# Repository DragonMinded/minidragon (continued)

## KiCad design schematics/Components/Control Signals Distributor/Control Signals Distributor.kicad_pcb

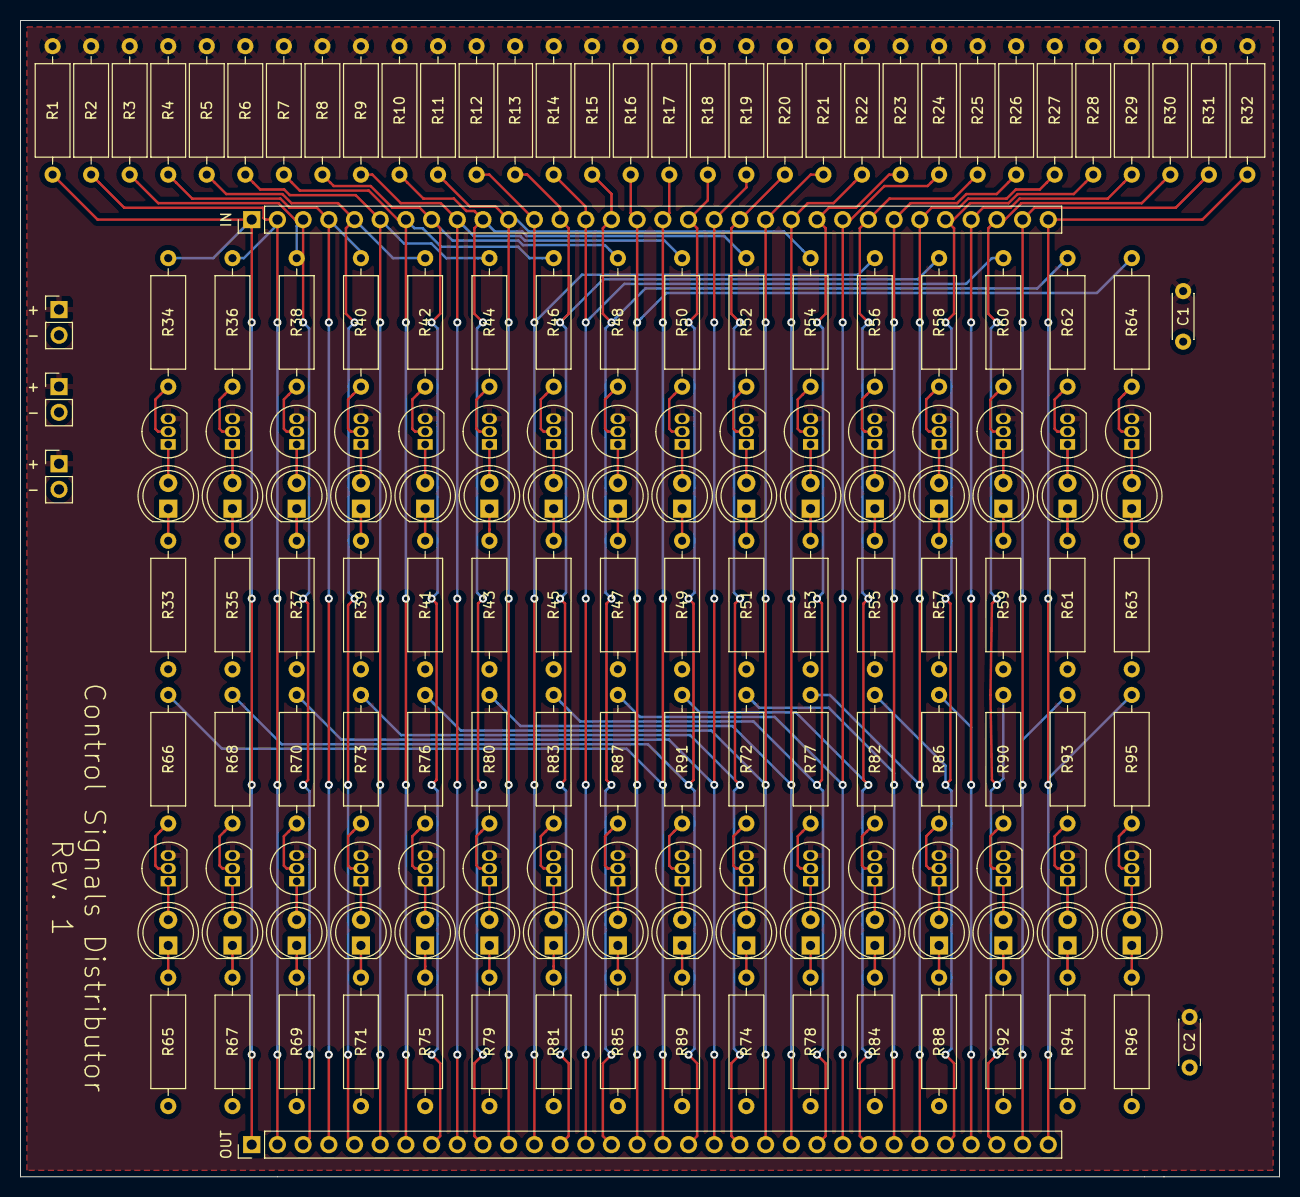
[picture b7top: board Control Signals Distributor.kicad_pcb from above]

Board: 2 copper layers, 124.5 x 114.3 mm, 167 parts (0 on the bottom side), 130 nets.

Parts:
C1, C2: 0.1uF; C_Disc_D4.3mm_W1.9mm_P5.00mm
D1, D2, D3, D4, D5, D6, D7, D8, D9, D10, D11, D12, D13, D14, D15, D16, D17, D18, D19, D20, D21, D22, D23, D24, D25, D26, D27, D28, D29, D30, D31, D32: LED; LED_D5.0mm
J1, J3, J4: POWER; PinHeader_1x02_P2.54mm_Vertical
J2: IN; PinHeader_1x32_P2.54mm_Vertical
J5: OUT; PinHeader_1x32_P2.54mm_Vertical
Q1, Q2, Q3, Q4, Q5, Q6, Q7, Q8, Q9, Q10, Q11, Q12, Q13, Q14, Q15, Q16, Q17, Q18, Q19, Q20, Q21, Q22, Q23, Q24, Q25, Q26, Q27, Q28, Q29, Q30, Q31, Q32: 2N2222; TO-92_Inline
R1, R2, R3, R4, R5, R6, R7, R8, R9, R10, R11, R12, R13, R14, R15, R16, R17, R18, R19, R20, R21, R22, R23, R24, R25, R26, R27, R28, R29, R30, R31, R32, R33, R35, R37, R39, R41, R43, R45, R47, R49, R51, R53, R55, R57, R59, R61, R63, R65, R67, R69, R71, R74, R75, R78, R79, R81, R84, R85, R88, R89, R92, R94, R96: 1K; R_Axial_DIN0309_L9.0mm_D3.2mm_P12.70mm_Horizontal
R34, R36, R38, R40, R42, R44, R46, R48, R50, R52, R54, R56, R58, R60, R62, R64, R66, R68, R70, R72, R73, R76, R77, R80, R82, R83, R86, R87, R90, R91, R93, R95: 10K; R_Axial_DIN0309_L9.0mm_D3.2mm_P12.70mm_Horizontal

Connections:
GND: C1.2, C2.2, J1.2, J3.2, J4.2, R33.2, R35.2, R37.2, R39.2, R41.2, R43.2, R45.2, R47.2, R49.2, R51.2, R53.2, R55.2, R57.2, R59.2, R61.2, R63.2, R65.2, R67.2, R69.2, R71.2, R74.2, R75.2, R78.2, R79.2, R81.2, R84.2, R85.2, R88.2, R89.2, R92.2, R94.2, R96.2
unnamed: D1.2 (A), Q1.1 (E)
unnamed: D1.1 (K), R33.1
unnamed: D2.2 (A), Q2.1 (E)
unnamed: D2.1 (K), R35.1
unnamed: D3.2 (A), Q3.1 (E)
unnamed: D3.1 (K), R37.1
unnamed: D4.2 (A), Q4.1 (E)
unnamed: D4.1 (K), R39.1
unnamed: D5.2 (A), Q5.1 (E)
unnamed: D5.1 (K), R41.1
unnamed: D6.2 (A), Q6.1 (E)
unnamed: D6.1 (K), R43.1
unnamed: D7.2 (A), Q7.1 (E)
unnamed: D7.1 (K), R45.1
unnamed: D8.2 (A), Q8.1 (E)
unnamed: D8.1 (K), R47.1
unnamed: D9.2 (A), Q9.1 (E)
unnamed: D9.1 (K), R49.1
unnamed: D10.2 (A), Q10.1 (E)
unnamed: D10.1 (K), R51.1
unnamed: D11.2 (A), Q11.1 (E)
unnamed: D11.1 (K), R53.1
unnamed: D12.2 (A), Q12.1 (E)
unnamed: D12.1 (K), R55.1
unnamed: D13.2 (A), Q13.1 (E)
unnamed: D13.1 (K), R57.1
unnamed: D14.2 (A), Q14.1 (E)
unnamed: D14.1 (K), R59.1
unnamed: D15.2 (A), Q15.1 (E)
unnamed: D15.1 (K), R61.1
unnamed: D16.2 (A), Q16.1 (E)
unnamed: D16.1 (K), R63.1
unnamed: D17.2 (A), Q17.1 (E)
unnamed: D17.1 (K), R65.1
unnamed: D18.2 (A), Q18.1 (E)
unnamed: D18.1 (K), R67.1
unnamed: D19.2 (A), Q19.1 (E)
unnamed: D19.1 (K), R69.1
unnamed: D20.2 (A), Q21.1 (E)
unnamed: D20.1 (K), R71.1
unnamed: D21.2 (A), Q20.1 (E)
unnamed: D21.1 (K), R74.1
unnamed: D22.2 (A), Q22.1 (E)
unnamed: D22.1 (K), R75.1
unnamed: D23.2 (A), Q23.1 (E)
unnamed: D23.1 (K), R78.1
unnamed: D24.2 (A), Q24.1 (E)
unnamed: D24.1 (K), R79.1
unnamed: D25.2 (A), Q26.1 (E)
unnamed: D25.1 (K), R81.1
unnamed: D26.2 (A), Q25.1 (E)
unnamed: D26.1 (K), R84.1
unnamed: D27.2 (A), Q28.1 (E)
unnamed: D27.1 (K), R85.1
unnamed: D28.2 (A), Q27.1 (E)
unnamed: D28.1 (K), R88.1
unnamed: D29.2 (A), Q30.1 (E)
unnamed: D29.1 (K), R89.1
unnamed: D30.2 (A), Q29.1 (E)
unnamed: D30.1 (K), R92.1
unnamed: D31.2 (A), Q31.1 (E)
unnamed: D31.1 (K), R94.1
unnamed: D32.2 (A), Q32.1 (E)
unnamed: D32.1 (K), R96.1
unnamed: J2.1, J5.1, R1.2, R34.1
unnamed: J2.2, J5.2, R2.2, R36.1
unnamed: J2.3, J5.3, R3.2, R38.1
unnamed: J2.4, J5.4, R4.2, R40.1
unnamed: J2.5, J5.5, R5.2, R42.1
unnamed: J2.6, J5.6, R6.2, R44.1
unnamed: J2.7, J5.7, R7.2, R46.1
unnamed: J2.8, J5.8, R8.2, R48.1
unnamed: J2.9, J5.9, R9.2, R50.1
unnamed: J2.10, J5.10, R10.2, R52.1
unnamed: J2.11, J5.11, R11.2, R54.1
unnamed: J2.12, J5.12, R12.2, R56.1
unnamed: J2.13, J5.13, R13.2, R58.1
unnamed: J2.14, J5.14, R14.2, R60.1
unnamed: J2.15, J5.15, R15.2, R62.1
unnamed: J2.16, J5.16, R16.2, R64.1
unnamed: J2.17, J5.17, R17.2, R66.1
unnamed: J2.18, J5.18, R18.2, R68.1
unnamed: J2.19, J5.19, R19.2, R70.1
unnamed: J2.20, J5.20, R20.2, R73.1
unnamed: J2.21, J5.21, R21.2, R76.1
unnamed: J2.22, J5.22, R22.2, R80.1
unnamed: J2.23, J5.23, R23.2, R83.1
unnamed: J2.24, J5.24, R24.2, R87.1
unnamed: J2.25, J5.25, R25.2, R91.1
unnamed: J2.26, J5.26, R26.2, R72.1
unnamed: J2.27, J5.27, R27.2, R77.1
unnamed: J2.28, J5.28, R28.2, R82.1
unnamed: J2.29, J5.29, R29.2, R86.1
unnamed: J2.30, J5.30, R30.2, R90.1
unnamed: J2.31, J5.31, R31.2, R93.1
unnamed: J2.32, J5.32, R32.2, R95.1
unnamed: Q1.2 (B), R34.2
unnamed: Q2.2 (B), R36.2
unnamed: Q3.2 (B), R38.2
unnamed: Q4.2 (B), R40.2
unnamed: Q5.2 (B), R42.2
unnamed: Q6.2 (B), R44.2
unnamed: Q7.2 (B), R46.2
unnamed: Q8.2 (B), R48.2
unnamed: Q9.2 (B), R50.2
unnamed: Q10.2 (B), R52.2
unnamed: Q11.2 (B), R54.2
unnamed: Q12.2 (B), R56.2
unnamed: Q13.2 (B), R58.2
unnamed: Q14.2 (B), R60.2
unnamed: Q15.2 (B), R62.2
unnamed: Q16.2 (B), R64.2
unnamed: Q17.2 (B), R66.2
unnamed: Q18.2 (B), R68.2
unnamed: Q19.2 (B), R70.2
unnamed: Q20.2 (B), R72.2
unnamed: Q21.2 (B), R73.2
unnamed: Q22.2 (B), R76.2
unnamed: Q23.2 (B), R77.2
unnamed: Q24.2 (B), R80.2
unnamed: Q25.2 (B), R82.2
unnamed: Q26.2 (B), R83.2
unnamed: Q27.2 (B), R86.2
unnamed: Q28.2 (B), R87.2
unnamed: Q29.2 (B), R90.2
unnamed: Q30.2 (B), R91.2
unnamed: Q31.2 (B), R93.2
unnamed: Q32.2 (B), R95.2
VCC: C1.1, C2.1, J1.1, J3.1, J4.1, Q1.3 (C), Q2.3 (C), Q3.3 (C), Q4.3 (C), Q5.3 (C), Q6.3 (C), Q7.3 (C), Q8.3 (C), Q9.3 (C), Q10.3 (C), Q11.3 (C), Q12.3 (C), Q13.3 (C), Q14.3 (C), Q15.3 (C), Q16.3 (C), Q17.3 (C), Q18.3 (C), Q19.3 (C), Q20.3 (C), Q21.3 (C), Q22.3 (C), Q23.3 (C), Q24.3 (C), Q25.3 (C), Q26.3 (C), Q27.3 (C), Q28.3 (C), Q29.3 (C), Q30.3 (C), Q31.3 (C), Q32.3 (C), R1.1, R2.1, R3.1, R4.1, R5.1, R6.1, R7.1, R8.1, R9.1, R10.1, R11.1, R12.1, R13.1, R14.1, R15.1, R16.1, R17.1, R18.1, R19.1, R20.1, R21.1, R22.1, R23.1, R24.1, R25.1, R26.1, R27.1, R28.1, R29.1, R30.1, R31.1, R32.1
